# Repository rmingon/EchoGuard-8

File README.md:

<h1 align="center">EchoGuard-8</h1>

<p align="center">
  <b>Eight GNSS receivers. One board. One trusted position.</b><br>
  An open hardware GNSS fusion array built around 8× ATGM336H receivers and an STM32F103,<br>
  with real-time outlier rejection and a single fused solution over SPI.
</p>

<p align="center">
  <a href="#why-an-array">Why an array</a> ·
  <a href="#how-it-works">How it works</a> ·
  <a href="#hardware">Hardware</a> ·
  <a href="#spi-interface">SPI interface</a> ·
  <a href="#arduino-library">Arduino library</a> ·
  <a href="#getting-started">Getting started</a> ·
  <a href="#roadmap">Roadmap</a>
</p>

---

## Why an array?

A single GNSS receiver gives you a position and asks you to trust it. When it suffers from
multipath, a weak antenna or a glitch, nothing tells you.

EchoGuard-8 runs **eight independent receivers side by side** and cross-checks them on every
GNSS epoch. That gives a host system three things a single receiver cannot:

| | |
| --- | --- |
| **Redundancy** | Any receiver can drop out. The fused solution keeps going with the others. |
| **Self-checking** | A receiver that drifts away from the consensus is detected, rejected, and benched if it keeps misbehaving. |
| **A trust signal** | Every output carries a status (`OK`, `DEGRADED`, `INTERFERENCE`, `NO_FIX`), the number of receivers used and their spread, so the host knows how much to rely on GNSS. |

Averaging also reduces the noise that is independent between receivers. Errors shared by all
of them (atmosphere, a jammer hitting every antenna) are not removed by averaging: for those,
the value of the array is in **detecting** the problem and telling the host.

## Highlights

- **8× ATGM336H** multi-constellation receivers, each with its own U.FL antenna input
- **STM32F103C8** running FreeRTOS: 3 hardware UARTs plus 5 timer-driven software UARTs
- **Epoch-aligned fusion**: only positions measured at the same GNSS instant are combined
- **Robust estimator**: median reference, HDOP-scaled outlier gate, inverse-variance weighting
- **Per-receiver health tracking** with automatic exclusion of faulty modules
- **C/N0 signal monitoring** on every receiver for interference diagnosis
- **32-byte CRC-protected SPI packet** for easy integration with a flight controller or SBC
- **Arduino library** with ready-to-run examples
- **4-layer PCB** with dedicated ground and power planes and per-module supply filtering
- **Live debug over SEGGER RTT**, no extra UART needed

## How it works

```mermaid
flowchart LR
    subgraph RX["8× ATGM336H"]
        direction TB
        G1["GNSS 1..3"]
        G2["GNSS 4..8"]
    end

    G1 -- "USART 1/2/3" --> P["NMEA parser<br>GGA · RMC · GSV"]
    G2 -- "software UART<br>TIM3, 8× oversampling" --> P

    P --> E["Epoch alignment<br>same UTC instant"]
    E --> M["Median reference<br>+ outlier gate"]
    M --> W["HDOP-weighted<br>average"]
    W --> S["Status and<br>health scoring"]

    S -- "SPI slave, 32-byte packet" --> H["Host<br>flight controller / SBC"]
    P -. "C/N0 per receiver" .-> D["RTT debug console"]
    S -.-> D
```

The fusion runs at 5 Hz and proceeds in five steps:

1. **Candidate selection.** A receiver is considered only if it has a valid fix, reported a
   position in the last 2 s, and is not currently benched by its fault score.
2. **Epoch alignment.** Fixes are grouped by the UTC time in their NMEA sentence (50 ms
   tolerance). The epoch reported by the most receivers wins, so positions measured at
   different instants are never mixed. A receiver that is one epoch late is skipped, not
   penalised.
3. **Outlier rejection.** The median latitude and longitude form a robust reference. A
   receiver is rejected when its horizontal distance to that reference exceeds
   `20 m + 15 m × HDOP` (clamped to 25..150 m).
4. **Weighted average.** The remaining receivers are combined with a weight of `1 / HDOP²`.
   Offsets are averaged around the median rather than absolute coordinates, which keeps
   single-precision floats exact to the centimetre.
5. **Status and health.** Each receiver carries a fault score that rises when it is rejected
   and decays when it agrees with the others. Above the limit, it is excluded from the
   solution. The result is then labelled:

| Status | Value | Meaning |
| --- | :---: | --- |
| `NO_FIX` | 0 | No usable receiver |
| `OK` | 1 | At least 4 receivers agree within 30 m, at most 1 rejected, average HDOP below 2.5 |
| `DEGRADED` | 2 | A solution exists but with reduced confidence |
| `INTERFERENCE` | 3 | 2 or more receivers rejected, spread above 80 m, or average HDOP above 5 |

### Signal monitoring

The firmware decodes the GSV sentences of every receiver and tracks its carrier-to-noise
density (C/N0) per constellation. The debug console prints, once per second, each receiver's
state and one summary line for the whole array:

```text
[gnss #3 U6 ] alive nmea=812 err=0 fix q=1 sats=9 hdop=0.95 lat=+48.8583000 lon=+2.2945000 cn0 top4=44.7 avg=40.2 max=47 trk=9/14 gps=6/9 bds=3/5
[cn0 array] modules=8 top4=43.9 min=41.2 (#5) max=45.8 (#2)
[fusion OK used=8 rej=0 hdop=98 res=142cm] lat=+48.8583012 lon=+2.2945004 alt=62.40m utc=12:35:19.000
```

`top4` is the mean of the four strongest satellites, a figure that barely depends on sky
geometry. If it drops on every receiver at once, interference is reaching all antennas. If it
is low on one receiver only, the cause is local: antenna, cable or routing.

## Hardware

| PCB layout | Schematic |
| :---: | :---: |
|  |  |

| | |
| --- | --- |
| **Receivers** | 8× ATGM336H, one U.FL antenna connector each |
| **MCU** | STM32F103C8T6 (Cortex-M3, 64 KB flash, 20 KB RAM) |
| **Stack-up** | 4 layers: signal / GND / +3.3 V / signal |
| **Supply** | Single regulated 3.3 V input, LC filter on every receiver |
| **Host link** | SPI slave on a 6-pin JST-SH connector (`J11`) |
| **Debug** | SWD header, reset and boot controls, one test point pair and one LED per receiver |
| **Storage** | One 24LC32 EEPROM on each receiver's I²C port |
| **Design tool** | KiCad |

### RF design choices

- A continuous ground plane directly under the top layer gives every RF trace a clean return path.
- Each receiver has its own filtered supply branch, so one module cannot inject noise into its neighbours.
- The MCU, the crystal and the SPI lines sit in the centre of the board, away from the antenna inputs on the edges.
- Antennas are remote (U.FL), so they can be placed where the sky view is best and away from noisy electronics.

### Receiver pin map

| Receiver | Reference | MCU RX pin | Link |
| :---: | :---: | :---: | --- |
| 1 | U1 | PB11 | USART3 |
| 2 | U4 | PA3 | USART2 |
| 3 | U6 | PB7 | USART1 (remapped) |
| 4 | U8 | PB9 | Software UART |
| 5 | U10 | PB13 | Software UART |
| 6 | U12 | PB15 | Software UART |
| 7 | U14 | PA5 | Software UART |
| 8 | U16 | PA7 | Software UART |

All receivers run at 9600 baud. The complete pin list is in [software/README.md](./software/README.md).

### ATGM336H at a glance

| Parameter | Value |
| --- | --- |
| Constellations | GPS, BeiDou, GLONASS, QZSS, SBAS |
| Positioning accuracy | ~2.5 m CEP |
| Cold start | < 35 s |
| Hot start | < 1 s |
| Update rate | Up to 10 Hz |
| Interface | UART (NMEA 0183) |
| Tracking current | ~26 mA |
| Operating temperature | -40 °C to +85 °C |

The full datasheet is included: [002176_ATGM336H.pdf](./002176_ATGM336H.pdf).

## SPI interface

EchoGuard-8 is an **SPI slave** (mode 0, MSB first). Each time the host asserts `SS`, the
board streams one 32-byte little-endian packet on `MISO`. The host can send a command on
`MOSI` in the same transaction, see below.

**Connector `J11` (JST-SH, 6 pins)**

| Pin | 1 | 2 | 3 | 4 | 5 | 6 |
| --- | :---: | :---: | :---: | :---: | :---: | :---: |
| Signal | `SS` (active low) | `MOSI` | `MISO` | `SCK` | `GND` | `+3.3V` |

**Packet layout**

| Offset | Type | Field | Description |
| :---: | :---: | --- | --- |
| 0 | `u32` | `magic` | `0x31464745`, ASCII `EGF1` |
| 4 | `u32` | `tick_ms` | Board uptime at the last fusion update |
| 8 | `i32` | `lat_e7` | Latitude, degrees × 10⁷ |
| 12 | `i32` | `lon_e7` | Longitude, degrees × 10⁷ |
| 16 | `i32` | `alt_cm` | Altitude, centimetres |
| 20 | `u16` | `avg_hdop_centi` | Average HDOP of the receivers used, × 100 |
| 22 | `u16` | `max_residual_cm` | Largest distance between a used receiver and the median, centimetres |
| 24 | `u8` | `status` | Fusion status, see the table above |
| 25 | `u8` | `used_modules` | Receivers used in this solution |
| 26 | `u8` | `rejected_modules` | Receivers rejected as outliers |
| 27 | `u8` | `has_fix` | 1 when the position is valid |
| 28 | `u8` | `commands_accepted` | Commands accepted since boot, mod 256 |
| 29 | `u8` | reserved | Zero |
| 30 | `u16` | `crc16` | CRC-16/CCITT-FALSE over bytes 0..29 |

**Commands**

The host sends a command in the first 8 bytes it clocks out on `MOSI` while reading a packet.
Anything else (all zeros for a plain read) is ignored. The command runs when `SS` rises, and
`commands_accepted` in the next packet goes up by one to acknowledge it.

| Offset | Type | Field | Description |
| :---: | :---: | --- | --- |
| 0 | `u32` | `magic` | `0x31434745`, ASCII `EGC1` |
| 4 | `u8` | `command` | `0x01`: reset the 8 GNSS receivers (shared nRESET, 10 ms pulse) |
| 5 | `u8` | `argument` | Zero |
| 6 | `u16` | `crc16` | CRC-16/CCITT-FALSE over bytes 0..5 |

**Timing**

The board builds the packet when `SS` falls and answers from an interrupt handler. Wait about
500 µs between asserting `SS` and the first clock edge, and start with a 100 kHz clock. The
solution is refreshed 5 times per second.

**Reading it from a Raspberry Pi**

`SS` is driven by hand here, because the Linux SPI driver gives no delay between chip select
and the first clock edge.

```python
import binascii
import struct
import time

import spidev
from gpiozero import DigitalOutputDevice

ss = DigitalOutputDevice(25, active_high=False, initial_value=False)  # SS on GPIO 25

spi = spidev.SpiDev()
spi.open(0, 0)
spi.no_cs = True
spi.mode = 0
spi.max_speed_hz = 100_000

ss.on()             # assert SS (drives the line low)
time.sleep(0.0005)  # let the board build the packet
packet = bytes(spi.xfer2([0] * 32))
ss.off()

(magic, tick_ms, lat_e7, lon_e7, alt_cm, hdop_centi, residual_cm,
 status, used, rejected, has_fix, commands, crc) = struct.unpack("<IIiiiHHBBBBBxH", packet)

if magic == 0x31464745 and crc == binascii.crc_hqx(packet[:30], 0xFFFF) and has_fix:
    print(f"{lat_e7 / 1e7:.7f}, {lon_e7 / 1e7:.7f}  alt {alt_cm / 100:.2f} m  "
          f"status {status}  {used} receivers used, {rejected} rejected")
```

## Arduino library

The [`EchoGuard8`](https://github.com/rmingon/EchoGuard8-Library) library reads the fused
solution from any Arduino board and handles the SPI timing, the CRC check and the decoding
for you.

```cpp
#include <EchoGuard8.h>

EchoGuard8 gnss(10);  // chip select pin

void setup() {
  Serial.begin(115200);
  gnss.begin();
}

void loop() {
  EchoGuard8Fix fix;
  if (gnss.read(fix) && fix.hasFix) {
    EchoGuard8::printDegrees(Serial, fix.latitudeE7);
    Serial.print(", ");
    EchoGuard8::printDegrees(Serial, fix.longitudeE7);
    Serial.print("  ");
    Serial.println(EchoGuard8::statusName(fix.status));
  }
  delay(1000);
}
```

It ships with four examples: `BasicRead`, `TrustMonitor` (status changes, link supervision,
LED), `Geofence` (distance to a home position with an alarm) and `PacketDump` (wiring
diagnostic). Wiring, API reference and troubleshooting are in the
[library repository](https://github.com/rmingon/EchoGuard8-Library#readme).

The library has its own repository and is included here as a git submodule. To fetch it with
the project, clone with `git clone --recurse-submodules`.

## Getting started

**You need:** an assembled board, 8 GNSS antennas with U.FL connectors, a regulated 3.3 V
supply, a J-Link compatible SWD probe, and [PlatformIO](https://platformio.org/).

```bash
git clone https://github.com/rmingon/EchoGuard-8.git
cd EchoGuard-8/software

pio run                      # build
pio run -t upload            # flash over SWD
python3 tools/rtt_read.py    # live debug console (SEGGER RTT)
```

Then connect `J11` to your host and start reading packets. Give the receivers a clear view of
the sky: a cold start takes around half a minute before the first fix.

## Built for FalconEdge

EchoGuard-8 is the positioning module of [FalconEdge](https://github.com/rmingon/Falcon-Edge),
a fixed-wing drone project. The eight antennas sit in a radial pattern in a dedicated bay on
top of the airframe.

## Project status

EchoGuard-8 is a prototype. The firmware builds and runs on the board; hardware bring-up and
field validation are in progress.

Known limitation of the current board revision: the external crystal does not start, so the
firmware runs from the internal oscillator (64 MHz through the PLL).

## Roadmap

- [ ] Use C/N0 as a fusion weight alongside HDOP
- [ ] Raise an interference flag when C/N0 drops on all receivers at once
- [ ] Route one PPS signal to the host connector for precise timestamping
- [ ] Add speed and course to the SPI packet
- [ ] Publish field results against a reference receiver

## Repository layout

```text
hardware/              KiCad project: schematic and PCB
software/              PlatformIO firmware (STM32Cube HAL + FreeRTOS)
  ├─ src/              GNSS drivers, NMEA parser, fusion, SPI output
  ├─ include/          Public headers
  └─ tools/            RTT debug reader
arduino/
  └─ EchoGuard8/       Arduino library for host boards (git submodule)
002176_ATGM336H.pdf    Receiver datasheet
licence.md             CERN-OHL-S v2 licence text
```

## Contributing

Issues and pull requests are welcome, whether for the hardware, the firmware or the
documentation. If you build a board, share your results: field data from other locations is
especially valuable.

## License

EchoGuard-8 is released under the **CERN Open Hardware Licence Version 2, Strongly
Reciprocal** (CERN-OHL-S v2). See [licence.md](./licence.md) for the full text.

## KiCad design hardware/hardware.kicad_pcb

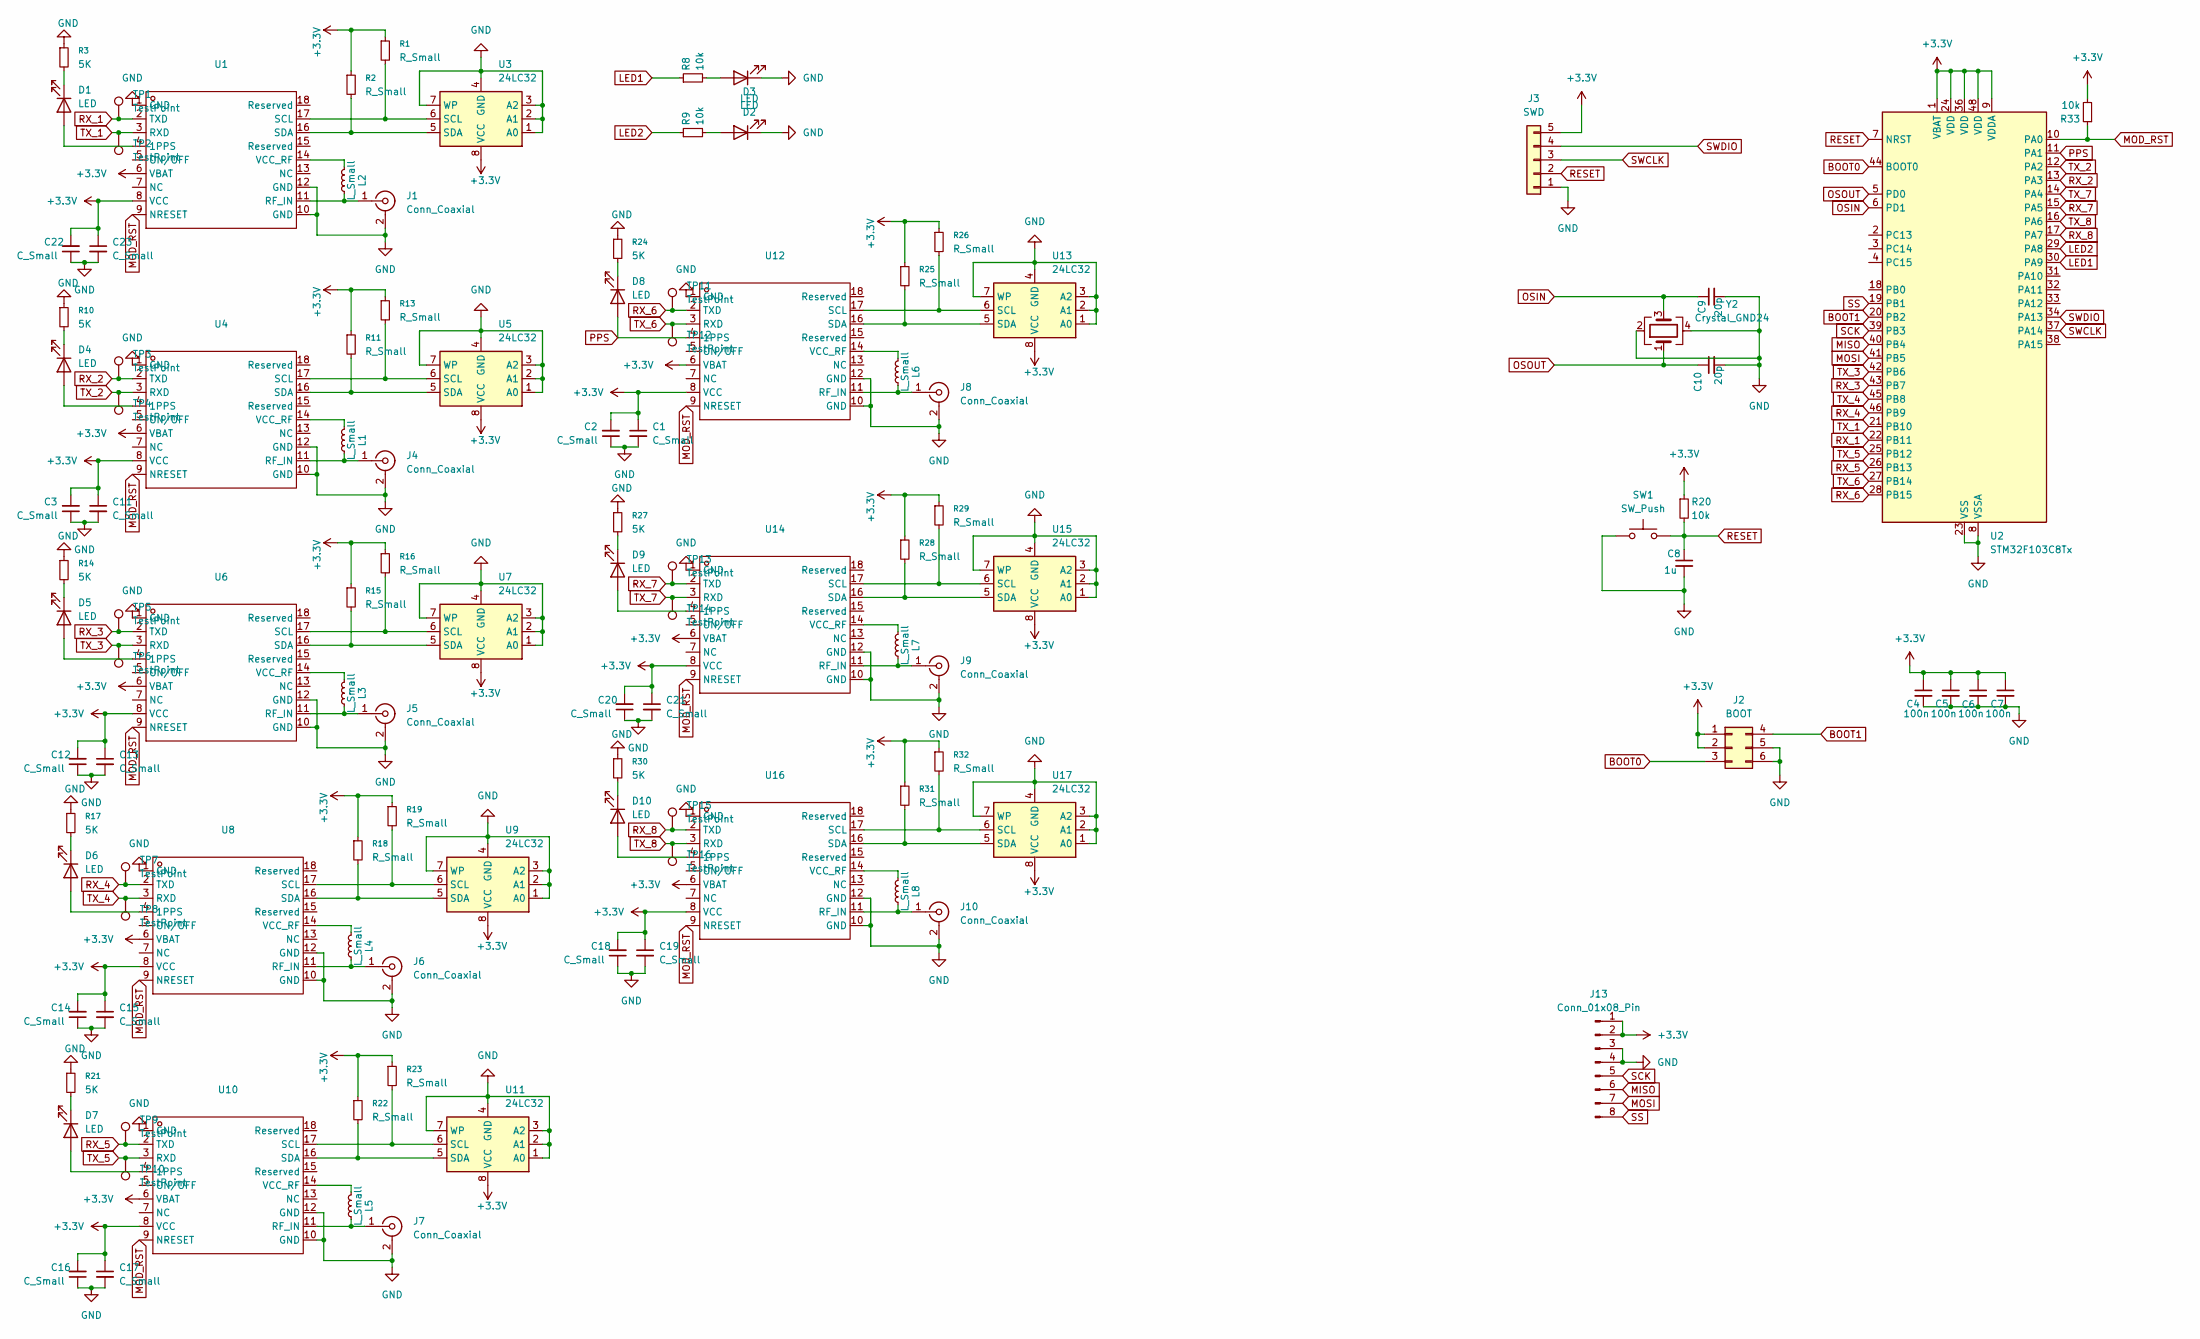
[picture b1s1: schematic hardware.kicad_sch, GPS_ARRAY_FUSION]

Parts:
C1, C11, C13, C15, C17, C19, C21, C23: C_Small; C_0603_1608Metric
C2, C3, C12, C14, C16, C18, C20, C22: C_Small; C_1206_3216Metric
C4, C5, C6, C7: 100n; C_0603_1608Metric
C8: 1u; C_0603_1608Metric
C9, C10: 20p; C_0603_1608Metric
D1, D4, D5, D6, D7, D8, D9, D10: LED; LED_0603_1608Metric
D2, D3: LED; D_0603_1608Metric
J1, J4, J5, J6, J7, J8, J9, J10: Conn_Coaxial; U.FL_Molex_MCRF_73412-0110_Vertical
J2: BOOT; PinHeader_2x03_P2.54mm_Vertical
J3: SWD; PinHeader_1x05_P2.54mm_Vertical
J13: Conn_01x08_Pin; JST_SHL_SM08B-SHLS-TF_1x08-1MP_P1.00mm_Horizontal
L1, L2, L3, L4, L5, L6, L7, L8: L_Small; L_0603_1608Metric
R1, R2, R11, R13, R15, R16, R18, R19, R22, R23, R25, R26, R28, R29, R31, R32: R_Small; R_0603_1608Metric
R3, R10, R14, R17, R21, R24, R27, R30: 5K; R_0603_1608Metric
R8, R9, R20, R33: 10k; R_0603_1608Metric
SW1: SW_Push; SW_SPST_CK_RS282G05A3
TP1, TP2, TP3, TP4, TP5, TP6, TP7, TP8, TP9, TP10, TP11, TP12, TP13, TP14, TP15, TP16: TestPoint; TestPoint_Pad_D1.5mm
U1, U4, U6, U8, U10, U12, U14, U16: GPSM-SMD_ATGM336H-TR; Manufacturer Part ATGM336H-5N31; LCSC Part Name BDS/GNSS 全星座定位导航模块
U2: STM32F103C8Tx; LQFP-48_7x7mm_P0.5mm
U3, U5, U7, U9, U11, U13, U15, U17: 24LC32; SOIC-8_3.9x4.9mm_P1.27mm
Y2: Crystal_GND24; Crystal_SMD_3225-4Pin_3.2x2.5mm

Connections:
+3.3V: C1.1, C2.2, C3.2, C4.1, C5.1, C6.1, C7.1, C11.1, C12.2, C13.1, C14.2, C15.1, C16.2, C17.1, C18.2, C19.1, C20.2, C21.1, C22.2, C23.1, J2.1, J2.2, J3.5, J13.1, J13.2, R1.1, R2.1, R11.1, R13.1, R15.1, R16.1, R18.1, R19.1, R20.1, R22.1, R23.1, R25.1, R26.1, R28.1, R29.1, R31.1, R32.1, R33.2, U1.6 (VBAT), U1.8 (VCC), U2.1 (VBAT), U2.9 (VDDA), U2.24 (VDD), U2.36 (VDD), U2.48 (VDD), U3.8 (VCC), U4.6 (VBAT), U4.8 (VCC), U5.8 (VCC), U6.6 (VBAT), U6.8 (VCC), U7.8 (VCC), U8.6 (VBAT), U8.8 (VCC), U9.8 (VCC), U10.6 (VBAT), U10.8 (VCC), U11.8 (VCC), U12.6 (VBAT), U12.8 (VCC), U13.8 (VCC), U14.6 (VBAT), U14.8 (VCC), U15.8 (VCC), U16.6 (VBAT), U16.8 (VCC), U17.8 (VCC)
BOOT0: J2.3, U2.44 (BOOT0)
BOOT1: J2.4, U2.20 (PB2)
GND: C1.2, C2.1, C3.1, C4.2, C5.2, C6.2, C7.2, C8.2, C9.2, C10.2, C11.2, C12.1, C13.2, C14.1, C15.2, C16.1, C17.2, C18.1, C19.2, C20.1, C21.2, C22.1, C23.2, D2.1 (K), D3.1 (K), J1.2 (Ext), J2.5, J2.6, J3.1, J4.2 (Ext), J5.2 (Ext), J6.2 (Ext), J7.2 (Ext), J8.2 (Ext), J9.2 (Ext), J10.2 (Ext), J13.3, J13.4, R3.1, R10.1, R14.1, R17.1, R21.1, R24.1, R27.1, R30.1, SW1.1, U1.1 (GND), U1.10 (GND), U1.12 (GND), U2.8 (VSSA), U2.23 (VSS), U2.35 (VSS), U2.47 (VSS), U3.1 (A0), U3.2 (A1), U3.3 (A2), U3.4 (GND), U3.7 (WP), U4.1 (GND), U4.10 (GND), U4.12 (GND), U5.1 (A0), U5.2 (A1), U5.3 (A2), U5.4 (GND), U5.7 (WP), U6.1 (GND), U6.10 (GND), U6.12 (GND), U7.1 (A0), U7.2 (A1), U7.3 (A2), U7.4 (GND), U7.7 (WP), U8.1 (GND), U8.10 (GND), U8.12 (GND), U9.1 (A0), U9.2 (A1), U9.3 (A2), U9.4 (GND), U9.7 (WP), U10.1 (GND), U10.10 (GND), U10.12 (GND), U11.1 (A0), U11.2 (A1), U11.3 (A2), U11.4 (GND), U11.7 (WP), U12.1 (GND), U12.10 (GND), U12.12 (GND), U13.1 (A0), U13.2 (A1), U13.3 (A2), U13.4 (GND), U13.7 (WP), U14.1 (GND), U14.10 (GND), U14.12 (GND), U15.1 (A0), U15.2 (A1), U15.3 (A2), U15.4 (GND), U15.7 (WP), U16.1 (GND), U16.10 (GND), U16.12 (GND), U17.1 (A0), U17.2 (A1), U17.3 (A2), U17.4 (GND), U17.7 (WP), Y2.2, Y2.4
LED1: R8.1, U2.30 (PA9)
LED2: R9.1, U2.29 (PA8)
MISO: J13.6, U2.40 (PB4)
MOD_RST: R33.1, U1.9 (NRESET), U2.10 (PA0), U4.9 (NRESET), U6.9 (NRESET), U8.9 (NRESET), U10.9 (NRESET), U12.9 (NRESET), U14.9 (NRESET), U16.9 (NRESET)
MOSI: J13.7, U2.41 (PB5)
unnamed: D1.2 (A), U1.4 (1PPS)
unnamed: D1.1 (K), R3.2
unnamed: D2.2 (A), R8.2
unnamed: D3.2 (A), R9.2
unnamed: D4.2 (A), U4.4 (1PPS)
unnamed: D4.1 (K), R10.2
unnamed: D5.2 (A), U6.4 (1PPS)
unnamed: D5.1 (K), R14.2
unnamed: D6.2 (A), U8.4 (1PPS)
unnamed: D6.1 (K), R17.2
unnamed: D7.2 (A), U10.4 (1PPS)
unnamed: D7.1 (K), R21.2
unnamed: D8.1 (K), R24.2
unnamed: D9.2 (A), U14.4 (1PPS)
unnamed: D9.1 (K), R27.2
unnamed: D10.2 (A), U16.4 (1PPS)
unnamed: D10.1 (K), R30.2
unnamed: J1.1 (In), L2.1, U1.11 (RF_IN)
unnamed: J4.1 (In), L1.1, U4.11 (RF_IN)
unnamed: J5.1 (In), L3.1, U6.11 (RF_IN)
unnamed: J6.1 (In), L4.1, U8.11 (RF_IN)
unnamed: J7.1 (In), L5.1, U10.11 (RF_IN)
unnamed: J8.1 (In), L6.1, U12.11 (RF_IN)
unnamed: J9.1 (In), L7.1, U14.11 (RF_IN)
unnamed: J10.1 (In), L8.1, U16.11 (RF_IN)
unnamed: R1.2, U1.17 (SCL), U3.6 (SCL)
unnamed: R2.2, U1.16 (SDA), U3.5 (SDA)
unnamed: L2.2, U1.14 (VCC_RF)
unnamed: R13.2, U4.17 (SCL), U5.6 (SCL)
unnamed: R11.2, U4.16 (SDA), U5.5 (SDA)
unnamed: L1.2, U4.14 (VCC_RF)
unnamed: R16.2, U6.17 (SCL), U7.6 (SCL)
unnamed: R15.2, U6.16 (SDA), U7.5 (SDA)
unnamed: L3.2, U6.14 (VCC_RF)
unnamed: R19.2, U8.17 (SCL), U9.6 (SCL)
unnamed: R18.2, U8.16 (SDA), U9.5 (SDA)
unnamed: L4.2, U8.14 (VCC_RF)
unnamed: R23.2, U10.17 (SCL), U11.6 (SCL)
unnamed: R22.2, U10.16 (SDA), U11.5 (SDA)
unnamed: L5.2, U10.14 (VCC_RF)
unnamed: R26.2, U12.17 (SCL), U13.6 (SCL)
unnamed: R25.2, U12.16 (SDA), U13.5 (SDA)
unnamed: L6.2, U12.14 (VCC_RF)
unnamed: R29.2, U14.17 (SCL), U15.6 (SCL)
unnamed: R28.2, U14.16 (SDA), U15.5 (SDA)
unnamed: L7.2, U14.14 (VCC_RF)
unnamed: R32.2, U16.17 (SCL), U17.6 (SCL)
unnamed: R31.2, U16.16 (SDA), U17.5 (SDA)
unnamed: L8.2, U16.14 (VCC_RF)
OSIN: C9.1, U2.6 (PD1), Y2.3
OSOUT: C10.1, U2.5 (PD0), Y2.1
PPS: D8.2 (A), U2.11 (PA1), U12.4 (1PPS)
RESET: C8.1, J3.2, R20.2, SW1.2, U2.7 (NRST)
RX_1: TP1.1 (1_1), U1.2 (TXD), U2.22 (PB11)
RX_2: TP3.1 (1_1), U2.13 (PA3), U4.2 (TXD)
RX_3: TP5.1 (1_1), U2.43 (PB7), U6.2 (TXD)
RX_4: TP7.1 (1_1), U2.46 (PB9), U8.2 (TXD)
RX_5: TP9.1 (1_1), U2.26 (PB13), U10.2 (TXD)
RX_6: TP11.1 (1_1), U2.28 (PB15), U12.2 (TXD)
RX_7: TP13.1 (1_1), U2.15 (PA5), U14.2 (TXD)
RX_8: TP15.1 (1_1), U2.17 (PA7), U16.2 (TXD)
SCK: J13.5, U2.39 (PB3)
SS: J13.8, U2.19 (PB1)
SWCLK: J3.3, U2.37 (PA14)
SWDIO: J3.4, U2.34 (PA13)
TX_1: TP2.1 (1_1), U1.3 (RXD), U2.21 (PB10)
TX_2: TP4.1 (1_1), U2.12 (PA2), U4.3 (RXD)
TX_3: TP6.1 (1_1), U2.42 (PB6), U6.3 (RXD)
TX_4: TP8.1 (1_1), U2.45 (PB8), U8.3 (RXD)
TX_5: TP10.1 (1_1), U2.25 (PB12), U10.3 (RXD)
TX_6: TP12.1 (1_1), U2.27 (PB14), U12.3 (RXD)
TX_7: TP14.1 (1_1), U2.14 (PA4), U14.3 (RXD)
TX_8: TP16.1 (1_1), U2.16 (PA6), U16.3 (RXD)

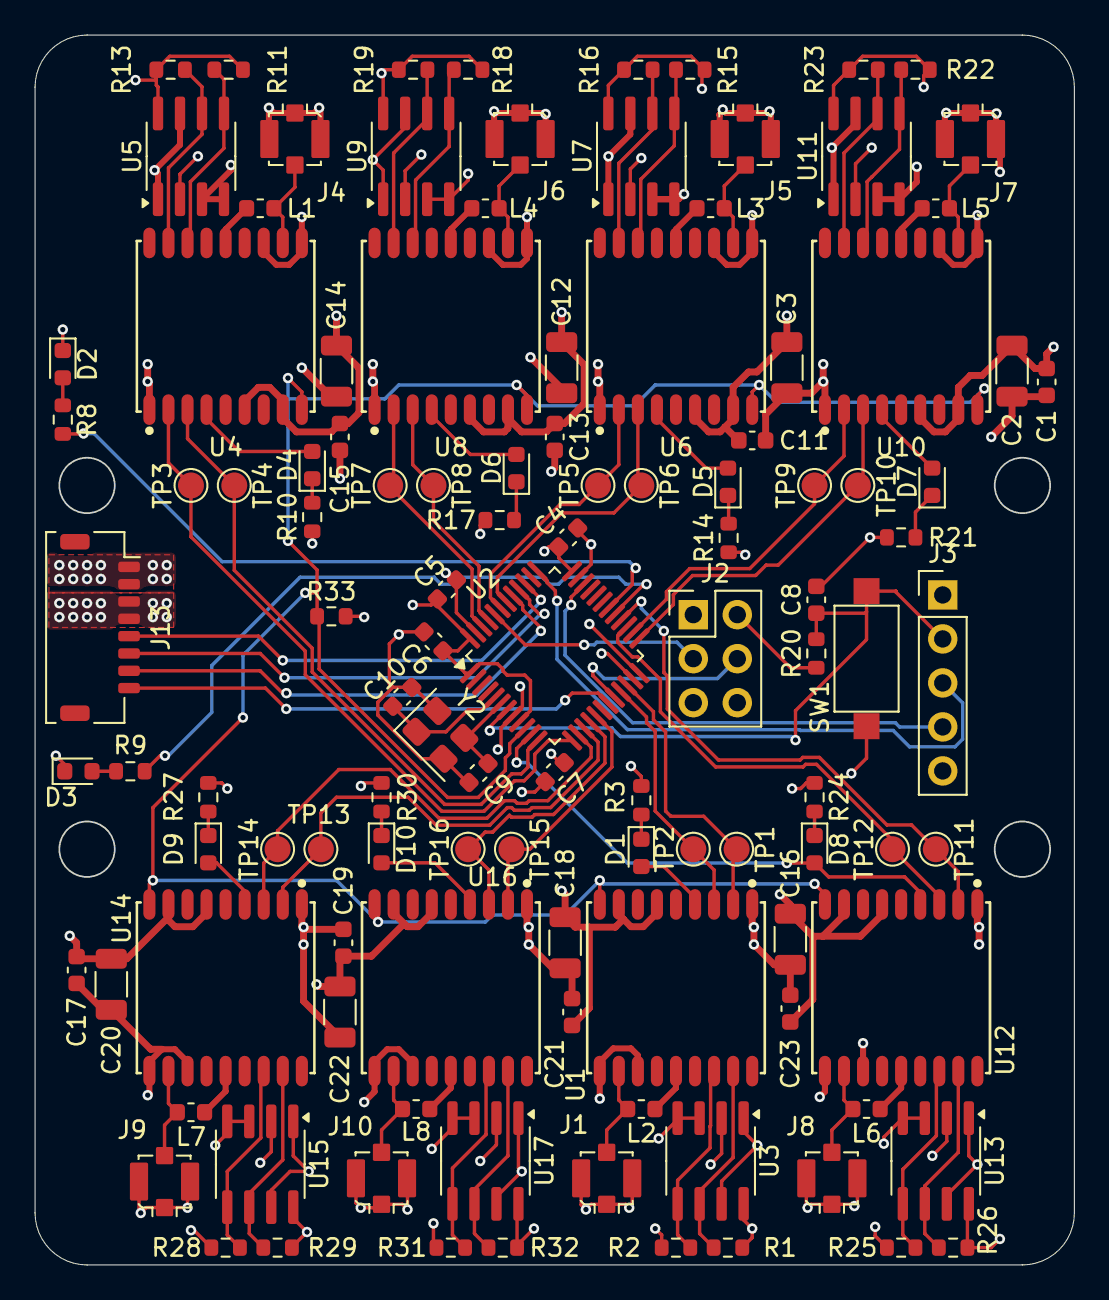
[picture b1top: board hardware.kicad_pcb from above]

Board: 4 copper layers, 60.0 x 71.0 mm, 115 parts (0 on the bottom side), 82 nets.

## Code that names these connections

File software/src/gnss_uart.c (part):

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	__HAL_RCC_GPIOA_CLK_ENABLE();
	__HAL_RCC_GPIOB_CLK_ENABLE();

	/* GNSS #3 uses USART1 remapped to PB6/PB7. */
	__HAL_AFIO_REMAP_USART1_ENABLE();

	for (size_t i = 0; i < GNSS_MODULE_COUNT; i++) {
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
	/*
	 * Note: only GNSS modules #1..#3 are wired to valid STM32F103 hardware USART pin pairs:
	 * - #1: USART3 (PB10/PB11)
	 * - #2: USART2 (PA2/PA3)
	 * - #3: USART1 remap (PB6/PB7)
	 *
	 * Modules #4..#8 require a software UART (or other acquisition method) if you intend to
	 * receive from all 8 modules concurrently.
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
	/*
	 * TIM3 only generates the sampling tick (update interrupt, no channel enabled), so its
	 * channel pins (PA6/PA7/PB0/PB1) keep their GPIO roles. TIM2 is left to the PPS capture.
	 *
	 * The timer counts the raw timer clock (no prescaler): at 64 MHz the tick period is
	 * rounded to 1/64 us, which keeps the baud error far below the UART tolerance.
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
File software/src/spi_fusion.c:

#include "spi_fusion.h"

#include <stddef.h>
#include <string.h>

#include "FreeRTOS.h"
#include "task.h"

#include "gnss.h"
#include "gnss_fusion.h"
#include "stm32f1xx_hal.h"

#define SPI_FUSION_MAGIC 0x31464745u /* 'EGF1' little-endian */

static volatile uint8_t tx_buf[SPI_FUSION_PACKET_SIZE];
static volatile uint8_t tx_index;
static volatile uint8_t selected;

static volatile uint8_t rx_buf[SPI_FUSION_PACKET_SIZE];
static volatile uint8_t rx_index;
static volatile uint8_t commands_accepted;

static uint16_t crc16_ccitt(const uint8_t *data, size_t len)
{
	uint16_t crc = 0xFFFFu;
	for (size_t i = 0; i < len; i++)
	{
		crc ^= (uint16_t)data[i] << 8;
		for (uint8_t b = 0; b < 8; b++)
		{
			if ((crc & 0x8000u) != 0)
			{
				crc = (uint16_t)((crc << 1) ^ 0x1021u);
			}
			else
			{
				crc <<= 1;
			}
		}
	}
	return crc;
}

static void put_u16_le(uint8_t *dst, uint16_t v)
{
	dst[0] = (uint8_t)(v & 0xFFu);
	dst[1] = (uint8_t)((v >> 8) & 0xFFu);
}

static void put_u32_le(uint8_t *dst, uint32_t v)
{
	dst[0] = (uint8_t)(v & 0xFFu);
	dst[1] = (uint8_t)((v >> 8) & 0xFFu);
	dst[2] = (uint8_t)((v >> 16) & 0xFFu);
	dst[3] = (uint8_t)((v >> 24) & 0xFFu);
}

static void put_i32_le(uint8_t *dst, int32_t v)
{
	put_u32_le(dst, (uint32_t)v);
}

static void build_packet_from_isr(uint8_t out[SPI_FUSION_PACKET_SIZE])
{
	GnssFusionResult r = {0};
	(void)GnssFusion_GetResultFromISR(&r);

	memset(out, 0, SPI_FUSION_PACKET_SIZE);
	put_u32_le(&out[0], SPI_FUSION_MAGIC);
	put_u32_le(&out[4], r.last_update_tick);
	put_i32_le(&out[8], r.lat_e7);
	put_i32_le(&out[12], r.lon_e7);
	put_i32_le(&out[16], r.alt_cm);
	put_u16_le(&out[20], r.avg_hdop_centi);
	put_u16_le(&out[22], r.max_residual_cm);
	out[24] = (uint8_t)r.status;
	out[25] = r.used_modules;
	out[26] = r.rejected_modules;
	out[27] = r.has_fix ? 1u : 0u;
	out[28] = commands_accepted;

	uint16_t crc = crc16_ccitt(out, SPI_FUSION_PACKET_SIZE - 2u);
	put_u16_le(&out[SPI_FUSION_PACKET_SIZE - 2u], crc);
}

static uint16_t get_u16_le(const uint8_t *src)
{
	return (uint16_t)(src[0] | ((uint16_t)src[1] << 8));
}

static uint32_t get_u32_le(const uint8_t *src)
{
	return (uint32_t)src[0] | ((uint32_t)src[1] << 8) | ((uint32_t)src[2] << 16) |
	       ((uint32_t)src[3] << 24);
}

static void store_rx_byte(uint8_t byte)
{
	if (rx_index < SPI_FUSION_PACKET_SIZE)
	{
		rx_buf[rx_index++] = byte;
	}
}

/* Called from the SS rising edge: run the command received during the transaction, if any. */
static void handle_command_from_isr(void)
{
	if (rx_index < SPI_COMMAND_SIZE)
	{
		return;
	}
	uint8_t frame[SPI_COMMAND_SIZE];
	for (size_t i = 0; i < SPI_COMMAND_SIZE; i++)
	{
		frame[i] = rx_buf[i];
	}
	if (get_u32_le(&frame[0]) != SPI_COMMAND_MAGIC ||
	    crc16_ccitt(frame, SPI_COMMAND_SIZE - 2u) != get_u16_le(&frame[SPI_COMMAND_SIZE - 2u]))
	{
		return;
	}

	switch (frame[4])
	{
	case SPI_COMMAND_RESET_MODULES:
		Gnss_RequestReset();
		break;
	default:
		return; /* Unknown command: not acknowledged. */
	}
	commands_accepted++;
}

void SpiFusion_Init(void)
{
	__HAL_RCC_AFIO_CLK_ENABLE();
	__HAL_RCC_GPIOB_CLK_ENABLE();
	__HAL_RCC_SPI1_CLK_ENABLE();

	/* PB3/PB4 are JTAG pins; free them while keeping SWD. */
	__HAL_AFIO_REMAP_SWJ_NOJTAG();
	__HAL_AFIO_REMAP_SPI1_ENABLE();

	/* J11 pinout:
	 * 1=SS(PB1), 2=MOSI(PB5), 3=MISO(PB4), 4=SCK(PB3), 5=GND, 6=+3.3V
	 */
	GPIO_InitTypeDef gpio = {0};

	gpio.Pin = GPIO_PIN_3 | GPIO_PIN_5;
	gpio.Mode = GPIO_MODE_INPUT;
	gpio.Pull = GPIO_NOPULL;
	HAL_GPIO_Init(GPIOB, &gpio);

	gpio.Pin = GPIO_PIN_4;
	gpio.Mode = GPIO_MODE_AF_PP;
	gpio.Pull = GPIO_NOPULL;
	gpio.Speed = GPIO_SPEED_FREQ_HIGH;
	HAL_GPIO_Init(GPIOB, &gpio);

	gpio.Pin = GPIO_PIN_1;
	gpio.Mode = GPIO_MODE_IT_RISING_FALLING;
	gpio.Pull = GPIO_PULLUP;
	HAL_GPIO_Init(GPIOB, &gpio);

	HAL_NVIC_SetPriority(EXTI1_IRQn, 6, 0);
	HAL_NVIC_EnableIRQ(EXTI1_IRQn);
	HAL_NVIC_SetPriority(SPI1_IRQn, 6, 0);
	HAL_NVIC_EnableIRQ(SPI1_IRQn);

	/* Configure SPI1 slave, 8-bit, Mode 0, software NSS forced selected (SSI=0). */
	SPI1->CR1 = 0;
	SPI1->CR2 = 0;
	SPI1->CR1 |= SPI_CR1_SSM; /* NSS managed in software. */
	SPI1->CR1 |= SPI_CR1_SSI; /* internal NSS high => not selected */
	SPI1->CR1 &= ~SPI_CR1_CPOL;
	SPI1->CR1 &= ~SPI_CR1_CPHA;
	SPI1->CR1 &= ~SPI_CR1_LSBFIRST;
	SPI1->CR1 &= ~SPI_CR1_MSTR;
	SPI1->CR1 &= ~SPI_CR1_DFF;

	/* Enable interrupts only while SS is asserted to avoid continuous TXE interrupts. */
	SPI1->CR2 |= SPI_CR2_ERRIE;
	SPI1->CR1 |= SPI_CR1_SPE;

	uint8_t packet[SPI_FUSION_PACKET_SIZE];
	build_packet_from_isr(packet);
	memcpy((void *)tx_buf, packet, sizeof(packet));
	tx_index = 0;
	selected = 0;
}

void SpiFusion_SpiIrqHandler(void)
{
	uint16_t sr = SPI1->SR;

	if ((sr & SPI_SR_RXNE) != 0)
	{
		uint8_t byte = (uint8_t)SPI1->DR;
		if (selected != 0)
		{
			store_rx_byte(byte);
		}
	}

	if ((sr & SPI_SR_TXE) != 0)
	{
		uint8_t byte = 0x00;
		if (selected != 0 && tx_index < SPI_FUSION_PACKET_SIZE)
		{
			byte = tx_buf[tx_index++];
		}
		SPI1->DR = byte;
	}

	if ((sr & SPI_SR_OVR) != 0)
	{
		(void)SPI1->DR;
		(void)SPI1->SR;
	}
}

void HAL_GPIO_EXTI_Callback(uint16_t gpio_pin)
{
	if (gpio_pin != GPIO_PIN_1)
	{
		return;
	}

	GPIO_PinState ss = HAL_GPIO_ReadPin(GPIOB, GPIO_PIN_1);

	if (ss == GPIO_PIN_RESET)
	{
		selected = 1;

		uint8_t packet[SPI_FUSION_PACKET_SIZE];
		build_packet_from_isr(packet);

		SPI1->CR2 &= ~(SPI_CR2_RXNEIE | SPI_CR2_TXEIE);
		(void)SPI1->DR;
		(void)SPI1->SR;
		SPI1->CR1 &= ~SPI_CR1_SSI; /* internal NSS low => selected */
		tx_index = 0;
		rx_index = 0;
		memcpy((void *)tx_buf, packet, sizeof(packet));
		if ((SPI1->SR & SPI_SR_TXE) != 0)
		{
			SPI1->DR = tx_buf[tx_index++];
		}
		SPI1->CR2 |= (SPI_CR2_RXNEIE | SPI_CR2_TXEIE);
	}
	else
	{
		SPI1->CR2 &= ~(SPI_CR2_RXNEIE | SPI_CR2_TXEIE);
		/* EXTI1 outranks SPI1 at equal priority: the last byte may still be waiting. */
		if (selected != 0 && (SPI1->SR & SPI_SR_RXNE) != 0)
		{
			store_rx_byte((uint8_t)SPI1->DR);
		}
		if (selected != 0)
		{
			handle_command_from_isr();
		}
		selected = 0;
		tx_index = 0;
		SPI1->CR1 |= SPI_CR1_SSI; /* internal NSS high => not selected */
		(void)SPI1->DR;
		(void)SPI1->SR;
	}
}

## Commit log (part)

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2025-09-27 add first gps footprint
2025-09-27 first wiring GPS with LNA
2025-09-27 place all components on pcb
2025-09-27 add power and comm connector
2025-09-28 full wiring pcb
2025-09-28 add pictures
2025-09-28 add connector step
2025-09-28 add readme
2025-09-28 add support image
2025-09-28 add pictures + licence
2025-12-27 add minimal firmware uart control
2025-12-27 fix led pin
2025-12-27 add light fusion system + debug printing
2025-12-27 add spi slave system
2025-12-28 fix gnss ground module

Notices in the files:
README.md:
License: CERN-OHL-S v2
